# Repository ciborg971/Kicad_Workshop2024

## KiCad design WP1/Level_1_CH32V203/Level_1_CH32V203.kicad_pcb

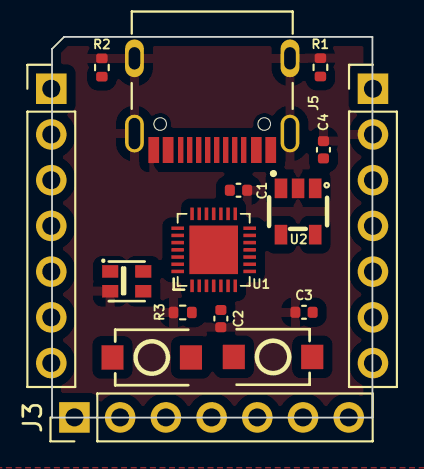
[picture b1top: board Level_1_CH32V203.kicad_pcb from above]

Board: 2 copper layers, 17.8 x 21.1 mm, 16 parts (0 on the bottom side), 29 nets, no tracks yet.

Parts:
C1, C2, C3: 100nF; C_0402_1005Metric
C4: 1uF; C_0402_1005Metric
J1, J2, J3: Conn_01x07_Pin; PinHeader_1x07_P2.54mm_Vertical
J5: TYPE-C-31-M-12; HRO_TYPE-C-31-M-12
LED1: WS2812B-2020; LED-SMD_4P-L2.0-W2.0-TL_WS2812B-2020
R1, R2, R3: 5K1; R_0402_1005Metric
SW1, SW2: TS-1088R-02026; SW-SMD_L3.9-W3.0-P4.45
U1: CH32V203G6U6; QFN-28_L4.0-W4.0-P0.40-BL-EP2.7
U2: RT9078-33GJ5; TSOT-23-5_L2.9-W1.6-P0.95-LS2.8-BR

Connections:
+3.3V: C1.1, C2.1, J2.3, LED1.4 (VDD), SW1.1, U1.5 (VDDA), U1.17 (VDD), U2.5 (VOUT)
/I2C_SCL: J1.6, U1.27 (PB6)
/I2C_SDA: J1.5, U1.28 (PB7)
/LED_OUTPUT: J3.7, LED1.1 (DO)
/PA0: J1.4, U1.6 (PA0/WKUP/ADC0)
/PA1: J1.3, U1.7 (PA1/ADC1)
/PA13: J3.6, U1.21 (PA13/SWDIO)
/PA14: J3.5, U1.22 (PA14/SWCLK)
/PA15: J3.4, U1.23 (PA15)
/PB0: J1.2, U1.14 (PB0/ADC8)
/PB1: J1.1, U1.15 (PB1/ADC9)
/PB3: J3.3, U1.24 (PB3)
/PB4: J3.2, U1.25 (PB4)
/PB5: J3.1, U1.26 (PB5)
/PD0: LED1.3 (DI), U1.2 (OSC_IN/PD0)
/SPI_MISO: J2.5, U1.12 (PA6/ADC6)
/SPI_MOSI: J2.4, U1.13 (PA7/ADC7)
/SPI_SCK: J2.6, U1.11 (PA5/ADC5)
/UART_RX: J2.7, U1.9 (PA3/ADC3)
/UART_TX: J1.7, U1.8 (PA2/ADC2)
/USB_DN: J5.A7 (DN1), J5.B7 (DN2), U1.19 (PA10/PA11/USB1DM)
/USB_DP: J5.A6 (DP1), J5.B6 (DP2), U1.20 (PA12/USB1DP)
GND: C1.2, C2.2, C3.1, C4.2, J2.2, J5.A1B12 (GND), J5.B1A12 (GND), J5.S1 (SHIELD), J5.S2 (SHIELD), J5.S3 (SHIELD), J5.S4 (SHIELD), LED1.2 (GND), R1.1, R2.2, R3.1, U1.16 (VSS), U1.29 (VSS), U2.2 (GND)
unnamed: C3.2, SW2.1
unnamed: J5.A5 (CC1), R1.2
unnamed: J5.B5 (CC2), R2.1
unnamed: R3.2, SW1.2, U1.1 (BOOT0/PB8)
unnamed: SW2.2, U1.4 (NRST)
VBUS: C4.1, J2.1, J5.A4B9 (VBUS), J5.B4A9 (VBUS), U2.1 (VIN), U2.3 (EN)

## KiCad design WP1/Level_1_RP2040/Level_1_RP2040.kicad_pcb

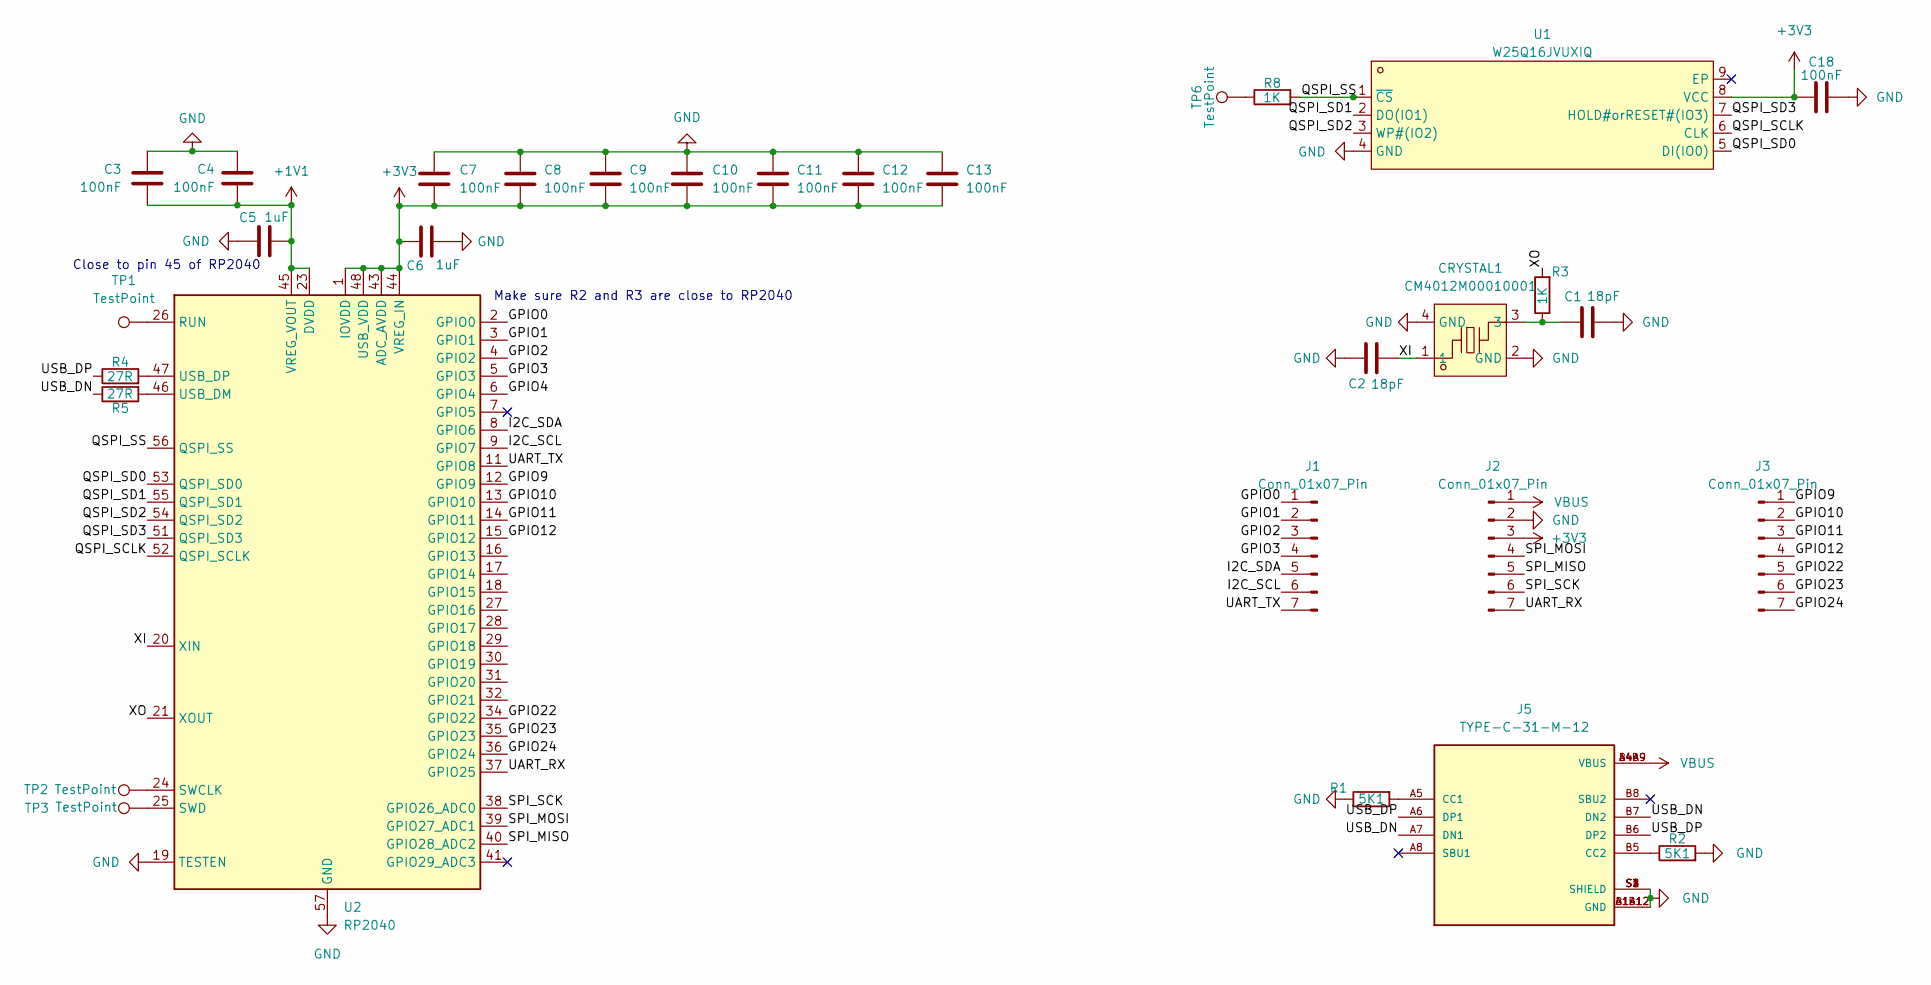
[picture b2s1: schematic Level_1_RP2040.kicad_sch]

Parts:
C1, C2: 18pF; C_0402_1005Metric; LCSC C880644
C3, C4, C7, C9, C10, C11, C12, C13, C18: 100nF; C_0402_1005Metric; LCSC C392963
C5, C6: 1uF; C_0402_1005Metric; LCSC C92755
C8: 100nF; C_0402_1005Metric
CRYSTAL1: CM4012M00010001; CRYSTAL-SMD_4P-L2.5-W2.0-BL; LCSC Part C7294610
J1, J2, J3: Conn_01x07_Pin; PinHeader_1x07_P2.54mm_Vertical
J5: TYPE-C-31-M-12; HRO_TYPE-C-31-M-12; PARTREV A
R1, R2: 5K1; R_0201_0603Metric; LCSC C328327
R3, R8: 1K; R_0201_0603Metric; LCSC C242161
R4, R5: 27R; R_0201_0603Metric; LCSC C227342
TP1, TP2, TP3, TP6: TestPoint; TestPoint_Pad_D1.5mm
U1: W25Q16JVUXIQ; USON-8_L3.0-W2.0-P0.50-BL-EP; LCSC Part C2843335
U2: RP2040; QFN-56-1EP_7x7mm_P0.4mm_EP3.2x3.2mm

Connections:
+1V1: C3.1, C4.1, C5.2, U2.23 (DVDD), U2.45 (VREG_VOUT), U2.50 (DVDD)
+3V3: C6.1, C7.2, C8.2, C9.2, C10.2, C11.2, C12.2, C13.2, C18.2, J2.3, U1.8 (VCC), U2.1 (IOVDD), U2.10 (IOVDD), U2.22 (IOVDD), U2.33 (IOVDD), U2.42 (IOVDD), U2.43 (ADC_AVDD), U2.44 (VREG_IN), U2.48 (USB_VDD), U2.49 (IOVDD)
/GPIO0: J1.1, U2.2 (GPIO0)
/GPIO1: J1.2, U2.3 (GPIO1)
/GPIO2: J1.3, U2.4 (GPIO2)
/GPIO3: J1.4, U2.5 (GPIO3)
/GPIO4: U2.6 (GPIO4)
/GPIO9: J3.1, U2.12 (GPIO9)
/GPIO10: J3.2, U2.13 (GPIO10)
/GPIO11: J3.3, U2.14 (GPIO11)
/GPIO12: J3.4, U2.15 (GPIO12)
/GPIO22: J3.5, U2.34 (GPIO22)
/GPIO23: J3.6, U2.35 (GPIO23)
/GPIO24: J3.7, U2.36 (GPIO24)
/I2C_SCL: J1.6, U2.9 (GPIO7)
/I2C_SDA: J1.5, U2.8 (GPIO6)
/QSPI_SCLK: U1.6 (CLK), U2.52 (QSPI_SCLK)
/QSPI_SD0: U1.5 (DI(IO0)), U2.53 (QSPI_SD0)
/QSPI_SD1: U1.2 (DO(IO1)), U2.55 (QSPI_SD1)
/QSPI_SD2: U1.3 (WP#(IO2)), U2.54 (QSPI_SD2)
/QSPI_SD3: U1.7 (HOLD#orRESET#(IO3)), U2.51 (QSPI_SD3)
/QSPI_SS: R8.2, U1.1 (~CS), U2.56 (QSPI_SS)
/SPI_MISO: J2.5, U2.40 (GPIO28_ADC2)
/SPI_MOSI: J2.4, U2.39 (GPIO27_ADC1)
/SPI_SCK: J2.6, U2.38 (GPIO26_ADC0)
/UART_RX: J2.7, U2.37 (GPIO25)
/UART_TX: J1.7, U2.11 (GPIO8)
/USB_DN: J5.A7 (DN1), J5.B7 (DN2), R5.1
/USB_DP: J5.A6 (DP1), J5.B6 (DP2), R4.1
/XI: C2.2, CRYSTAL1.1, U2.20 (XIN)
/XO: R3.2, U2.21 (XOUT)
GND: C1.2, C2.1, C3.2, C4.2, C5.1, C6.2, C7.1, C8.1, C9.1, C10.1, C11.1, C12.1, C13.1, C18.1, CRYSTAL1.2 (GND), CRYSTAL1.4 (GND), J2.2, J5.A1B12 (GND), J5.B1A12 (GND), J5.S1 (SHIELD), J5.S2 (SHIELD), J5.S3 (SHIELD), J5.S4 (SHIELD), R1.1, R2.2, U1.4 (GND), U2.19 (TESTEN), U2.57 (GND)
unnamed: C1.1, CRYSTAL1.3, R3.1
unnamed: J5.A5 (CC1), R1.2
unnamed: J5.B5 (CC2), R2.1
unnamed: R8.1, TP6.1
unnamed: TP1.1, U2.26 (RUN)
unnamed: TP2.1, U2.24 (SWCLK)
unnamed: TP3.1, U2.25 (SWD)
unnamed: R5.2, U2.46 (USB_DM)
unnamed: R4.2, U2.47 (USB_DP)
VBUS: J2.1, J5.A4B9 (VBUS), J5.B4A9 (VBUS)

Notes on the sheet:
Close to pin 45 of RP2040
Make sure R2 and R3 are close to RP2040

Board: 4 copper layers, 31 parts (20 on the bottom side), 41 nets, no tracks yet.

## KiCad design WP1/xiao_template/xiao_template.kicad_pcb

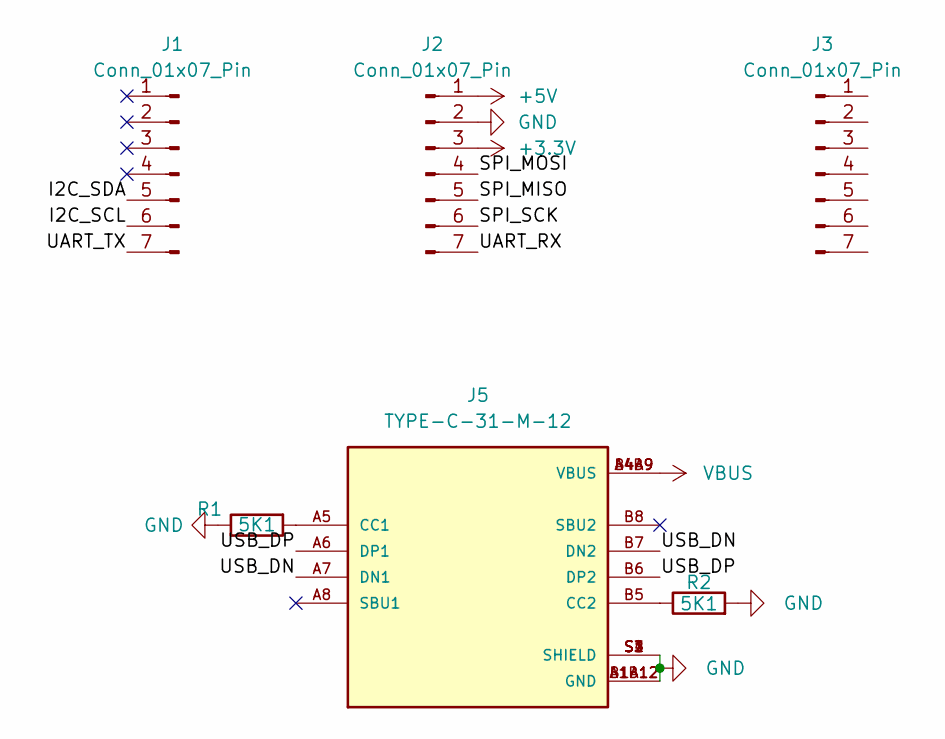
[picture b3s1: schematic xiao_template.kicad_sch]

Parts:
J1, J2, J3: Conn_01x07_Pin; PinHeader_1x07_P2.54mm_Vertical
J5: TYPE-C-31-M-12; HRO_TYPE-C-31-M-12; PARTREV A
R1, R2: 5K1; R_0402_1005Metric; LCSC C328327

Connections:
+3.3V: J2.3
+5V: J2.1
/I2C_SCL: J1.6
/I2C_SDA: J1.5
/SPI_MISO: J2.5
/SPI_MOSI: J2.4
/SPI_SCK: J2.6
/UART_RX: J2.7
/UART_TX: J1.7
/USB_DN: J5.A7 (DN1), J5.B7 (DN2)
/USB_DP: J5.A6 (DP1), J5.B6 (DP2)
GND: J2.2, J5.A1B12 (GND), J5.B1A12 (GND), J5.S1 (SHIELD), J5.S2 (SHIELD), J5.S3 (SHIELD), J5.S4 (SHIELD), R1.1, R2.2
unnamed: J5.A5 (CC1), R1.2
unnamed: J5.B5 (CC2), R2.1
VBUS: J5.A4B9 (VBUS), J5.B4A9 (VBUS)

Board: 2 copper layers, 6 parts (0 on the bottom side), 6 nets, no tracks yet.

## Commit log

2024-11-19 Create LICENSE
2024-11-19 add files for Level_1_RP2040 project
2024-11-19 add files for Level_1_CH32V203 project
    TODO for Level_1_RP2040 :
    - Choose correctly capacitor for crystal
    - 3.3V regulator
    - ground plane
